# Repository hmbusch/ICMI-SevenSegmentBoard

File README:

=====================================================================
= ICMI Seven-Segment Board                                          =
=====================================================================
* Author          : Hendrik Busch
* Current version : 1.1
* License         : Creative Commons Attribution-NonCommercial-
                    ShareAlike 3.0 Germany License.

The Seven-Segment Board offers up to 8 seven-segment digits with a
control circuit made up of several cheap and easy to obtain
components.

+++++++++++++++++++++++++++++++++++++++++++++++++++++++++++++++++++++
WARNING: The current board still has a design flaw. Since the ULN2803
and the 2N7002 each incur a voltage drop when active, 5 volts is not
really enough to light the display properly when driving high refresh 
rates for the POV effect. The first counter measure given the current
design is to insert lower current limiting resistors (say 10 ohms 
instead of 150). The other measure would be to increase the voltage,
but with the current design voltage can only be increased to 7 volts
as this is the maximum voltage for the shift register and the decade
counter. So an increase from 5 to 6 volts currently seems the most 
reasonable.
The next design iteration will feature seperated supply lines for the
LED segments and the TTL logic, just to make sure.
+++++++++++++++++++++++++++++++++++++++++++++++++++++++++++++++++++++

Seven-segment LED circuit
-------------------------
The board uses dual common anode seven-segment displays, meaning that
each component feature two digits with seven segments each. Each digit
has its own anode that is common to all segments in that digit (thus
common anode) and each segment has its own cathode, resulting in two 
anodes and 14 cathodes per component. Each segment cathode of a
digit is connected to all the other cathodes for this segment on
the other digits.
The LED circuit therefore features 8 anodes (one for each digit) and
7 cathodes (one for each segment).

Switching circuit
-----------------
The switching circuit uses a minimum of I/O 5 pins (excluding power).

Two are needed for a 74HC4017 decade counter that is responsible for
sourcing power to the digits, one at a time. Using a software timer,
the decade counter switches through each digit so fast, that the
human eye cannot distinguish between the single digits being turned
on and off but sees a steady display with all eight digits lit (this
is called the POV (persistence-of-vision) effect. Exploiting this
effect, the software and circuit only have to worry about displaying
a single digit at a time and switching between digits.

In order to control what each digit is actually displaying, a shift
register (74HC595) is used to set the state of each segment. As the
shift register is not made to sink current, it is connected to an
ULN2803A darlington array. If one of the shift register pins is HIGH,
the corresponding switch in the darlington array sinks the incoming
LED current on that pin, effectively lighting the corresponding 
segment.

The software must ensure that the digit switching and the segment
configuration are in sync, otherwise the display content may show
as distorted of shifted.

Version History
---------------

- v1.1
  - The CLEAR pin of the shift register is now connected to VCC and 
    not to GND as before. Pulling it to GND in v1.0 resulted in a
	continous purge of any data loaded into the register and thus
	rendering the display unusable.

- v1.0
  - Initial revision

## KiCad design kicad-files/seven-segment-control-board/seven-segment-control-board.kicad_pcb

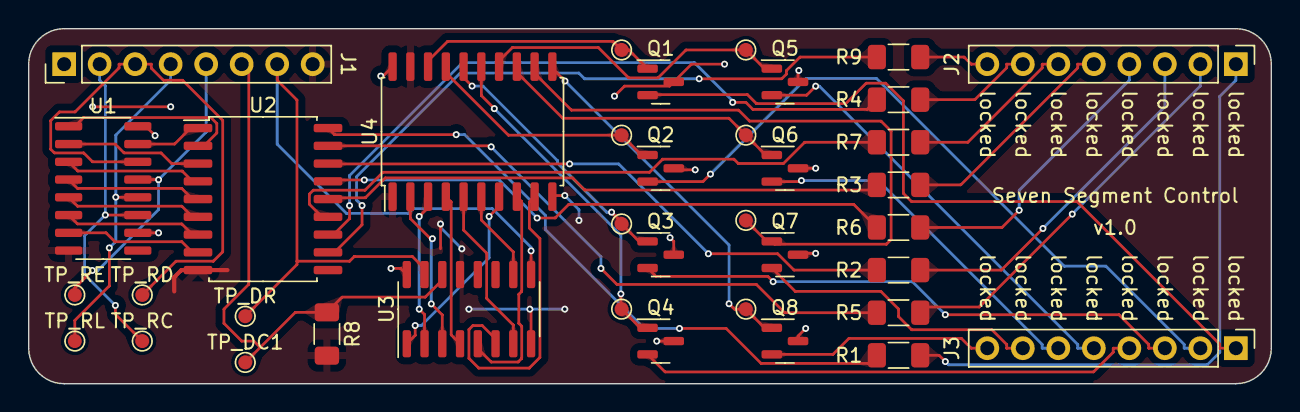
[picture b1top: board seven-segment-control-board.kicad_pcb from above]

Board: 2 copper layers, 88.9 x 25.4 mm, 38 parts (0 on the bottom side), 56 nets.

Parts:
J1: Input; PinHeader_1x08_P2.54mm_Vertical
J2: Segments; PinHeader_1x08_P2.54mm_Vertical
J3: Digits; PinHeader_1x08_P2.54mm_Vertical
Q1, Q2, Q3, Q4, Q5, Q6, Q7, Q8: BSS84; SOT-23
R1, R2, R3, R4, R5, R6, R7, R9: 150; R_1206_3216Metric_Pad1.30x1.75mm_HandSolder
R8: 10K; R_1206_3216Metric_Pad1.30x1.75mm_HandSolder
TP_DC1: TestPoint_Pad_D1.0mm
TP_DEC1, TP_DEC2, TP_DEC3, TP_DEC4, TP_DEC5, TP_DEC6, TP_DEC7, TP_DEC8: TestPoint_Pad_D1.0mm
TP_DR: TestPoint_Pad_D1.0mm
TP_RC: TestPoint_Pad_D1.0mm
TP_RD: TestPoint_Pad_D1.0mm
TP_RE: TestPoint_Pad_D1.0mm
TP_RL: TestPoint_Pad_D1.0mm
U1: 74HC595; SOIC-16_3.9x9.9mm_P1.27mm
U2: ULN2803A; SOIC-18W_7.5x11.6mm_P1.27mm
U3: 4017; SOIC-16_3.9x9.9mm_P1.27mm
U4: 74LS540; SOIC-20W_7.5x12.8mm_P1.27mm

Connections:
+5V: J1.1, Q1.3 (D), Q2.3 (D), Q3.3 (D), Q4.3 (D), Q5.3 (D), Q6.3 (D), Q7.3 (D), Q8.3 (D), U1.10 (~SRCLR), U1.16 (VCC), U3.16 (VDD), U4.20 (VCC)
/DEC_1: Q1.1 (G), TP_DEC1.1, U4.18 (Y0)
/DEC_2: Q2.1 (G), TP_DEC2.1, U4.17 (Y1)
/DEC_3: Q3.1 (G), TP_DEC3.1, U4.16 (Y2)
/DEC_4: Q4.1 (G), TP_DEC4.1, U4.15 (Y3)
/DEC_5: Q5.1 (G), TP_DEC5.1, U4.14 (Y4)
/DEC_6: Q6.1 (G), TP_DEC6.1, U4.13 (Y5)
/DEC_7: Q7.1 (G), TP_DEC7.1, U4.12 (Y6)
/DEC_8: Q8.1 (G), TP_DEC8.1, U4.11 (Y7)
/DEC_CLOCK: J1.6, R8.1, TP_DC1.1, U3.14 (CLK)
/DEC_RESET: J1.7, TP_DR.1, U3.9 (Q8), U3.15 (Reset)
/DIG_1: J3.1, Q1.2 (S)
/DIG_2: J3.2, Q2.2 (S)
/DIG_3: J3.3, Q3.2 (S)
/DIG_4: J3.4, Q4.2 (S)
/DIG_5: J3.5, Q5.2 (S)
/DIG_6: J3.6, Q6.2 (S)
/DIG_7: J3.7, Q7.2 (S)
/DIG_8: J3.8, Q8.2 (S)
/DP: J2.8, R9.1
/QA: U1.15 (QA), U2.1 (I1)
/QB: U1.1 (QB), U2.2 (I2)
/QC: U1.2 (QC), U2.3 (I3)
/QD: U1.3 (QD), U2.4 (I4)
/QE: U1.4 (QE), U2.5 (I5)
/QF: U1.5 (QF), U2.6 (I6)
/QG: U1.6 (QG), U2.7 (I7)
/QH: U1.7 (QH), U2.8 (I8)
/REG_CLOCK: J1.2, TP_RC.1, U1.11 (SRCLK)
/REG_DATA: J1.3, TP_RD.1, U1.14 (SER)
/REG_LATCH: J1.4, TP_RL.1, U1.12 (RCLK)
/SEG_A: J2.1, R1.1
/SEG_B: J2.2, R5.1
/SEG_C: J2.3, R2.1
/SEG_D: J2.4, R6.1
/SEG_E: J2.5, R3.1
/SEG_F: J2.6, R7.1
/SEG_G: J2.7, R4.1
/~REG_ENABLE: J1.5, TP_RE.1, U1.13 (~OE)
GND: J1.8, R8.2, U1.8 (GND), U2.9 (GND), U3.8 (VSS), U3.13 (CKEN), U4.1 (G1), U4.10 (GND), U4.19 (G2)
unnamed: R1.2, U2.18 (O1)
unnamed: R5.2, U2.17 (O2)
unnamed: R2.2, U2.16 (O3)
unnamed: R6.2, U2.15 (O4)
unnamed: R3.2, U2.14 (O5)
unnamed: R7.2, U2.13 (O6)
unnamed: R4.2, U2.12 (O7)
unnamed: R9.2, U2.11 (O8)
unnamed: U3.3 (Q0), U4.2 (A0)
unnamed: U3.2 (Q1), U4.3 (A1)
unnamed: U3.4 (Q2), U4.4 (A2)
unnamed: U3.7 (Q3), U4.5 (A3)
unnamed: U3.10 (Q4), U4.6 (A4)
unnamed: U3.1 (Q5), U4.7 (A5)
unnamed: U3.5 (Q6), U4.8 (A6)
unnamed: U3.6 (Q7), U4.9 (A7)

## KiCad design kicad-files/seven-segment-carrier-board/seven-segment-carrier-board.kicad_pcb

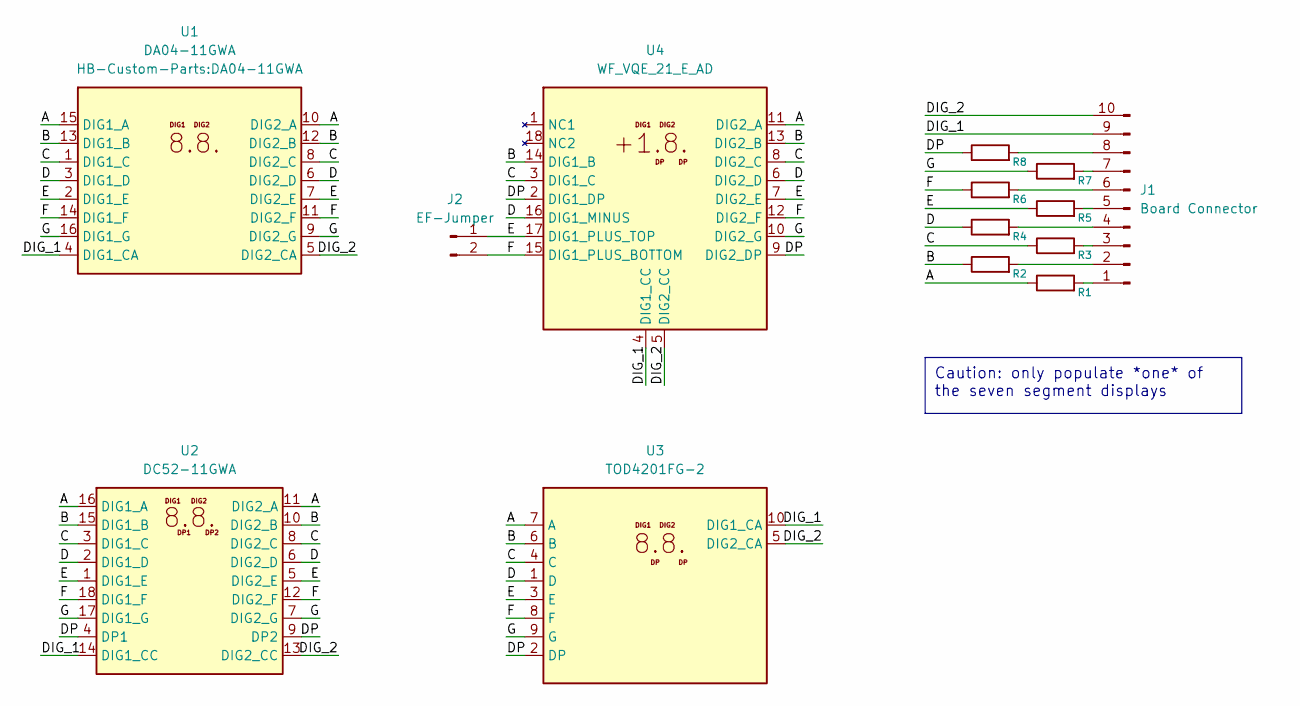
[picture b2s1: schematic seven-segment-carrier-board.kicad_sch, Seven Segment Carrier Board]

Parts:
J1: Board Connector; PinHeader_1x10_P2.54mm_Vertical
J2: EF-Jumper; SolderJumper-2_P1.3mm_Open_RoundedPad1.0x1.5mm
R1, R2, R3, R4, R5, R6, R7, R8: R; R_1206_3216Metric
U1: DA04-11GWA
U2: DC52-11GWA
U3: TOD4201FG-2
U4: WF_VQE_21_E_AD

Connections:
/A: R1.1, U1.10 (DIG2_A), U1.15 (DIG1_A), U2.11 (DIG2_A), U2.16 (DIG1_A), U3.7 (A), U4.11 (DIG2_A)
/B: R2.1, U1.12 (DIG2_B), U1.13 (DIG1_B), U2.10 (DIG2_B), U2.15 (DIG1_B), U3.6 (B), U4.13 (DIG2_B), U4.14 (DIG1_B)
/C: R3.1, U1.1 (DIG1_C), U1.8 (DIG2_C), U2.3 (DIG1_C), U2.8 (DIG2_C), U3.4 (C), U4.3 (DIG1_C), U4.8 (DIG2_C)
/D: R4.1, U1.3 (DIG1_D), U1.6 (DIG2_D), U2.2 (DIG1_D), U2.6 (DIG2_D), U3.1 (D), U4.6 (DIG2_D), U4.16 (DIG1_MINUS)
/DIG_1: J1.9, U1.4 (DIG1_CA), U2.14 (DIG1_CC), U3.10 (DIG1_CA), U4.4 (DIG1_CC)
/DIG_2: J1.10, U1.5 (DIG2_CA), U2.13 (DIG2_CC), U3.5 (DIG2_CA), U4.5 (DIG2_CC)
/DP: R8.1, U2.4 (DP1), U2.9 (DP2), U3.2 (DP), U4.2 (DIG1_DP), U4.9 (DIG2_DP)
/E: J2.1, R5.1, U1.2 (DIG1_E), U1.7 (DIG2_E), U2.1 (DIG1_E), U2.5 (DIG2_E), U3.3 (E), U4.7 (DIG2_E), U4.17 (DIG1_PLUS_TOP)
/F: J2.2, R6.1, U1.11 (DIG2_F), U1.14 (DIG1_F), U2.12 (DIG2_F), U2.18 (DIG1_F), U3.8 (F), U4.12 (DIG2_F), U4.15 (DIG1_PLUS_BOTTOM)
/G: R7.1, U1.9 (DIG2_G), U1.16 (DIG1_G), U2.7 (DIG2_G), U2.17 (DIG1_G), U3.9 (G), U4.10 (DIG2_G)
unnamed: J1.1, R1.2
unnamed: J1.2, R2.2
unnamed: J1.3, R3.2
unnamed: J1.4, R4.2
unnamed: J1.5, R5.2
unnamed: J1.6, R6.2
unnamed: J1.7, R7.2
unnamed: J1.8, R8.2

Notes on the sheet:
Caution: only populate *one* of the seven segment displays

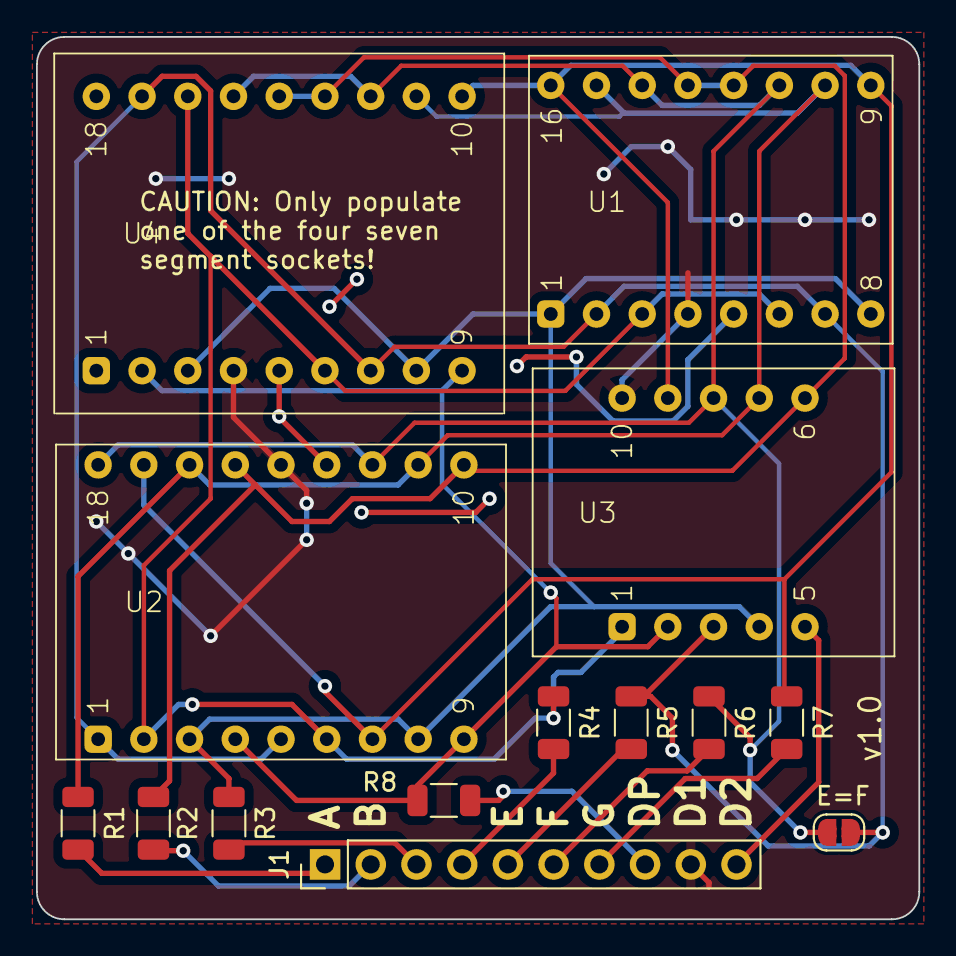
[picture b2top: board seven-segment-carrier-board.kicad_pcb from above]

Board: 2 copper layers, 49.0 x 49.0 mm, 14 parts (0 on the bottom side), 18 nets.

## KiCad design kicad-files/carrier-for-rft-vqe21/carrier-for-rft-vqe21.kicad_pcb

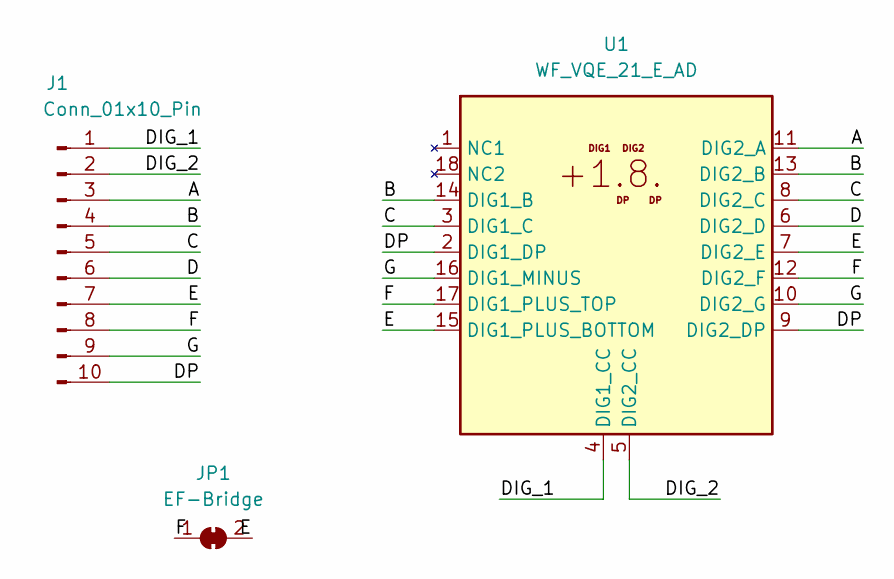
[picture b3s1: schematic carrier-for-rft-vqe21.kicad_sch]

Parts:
J1: Conn_01x10_Pin; PinHeader_1x10_P2.54mm_Vertical
JP1: EF-Bridge; SolderJumper-2_P1.3mm_Bridged_Pad1.0x1.5mm
U1: WF_VQE_21_E_AD; WF_VQE_21_E_AD_less_silk

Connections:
/A: J1.3, U1.11 (DIG2_A)
/B: J1.4, U1.13 (DIG2_B), U1.14 (DIG1_B)
/C: J1.5, U1.3 (DIG1_C), U1.8 (DIG2_C)
/D: J1.6, U1.6 (DIG2_D)
/DIG_1: J1.1, U1.4 (DIG1_CC)
/DIG_2: J1.2, U1.5 (DIG2_CC)
/DP: J1.10, U1.2 (DIG1_DP), U1.9 (DIG2_DP)
/E: J1.7, JP1.2 (B), U1.7 (DIG2_E), U1.15 (DIG1_PLUS_BOTTOM)
/F: J1.8, JP1.1 (A), U1.12 (DIG2_F), U1.17 (DIG1_PLUS_TOP)
/G: J1.9, U1.10 (DIG2_G), U1.16 (DIG1_MINUS)

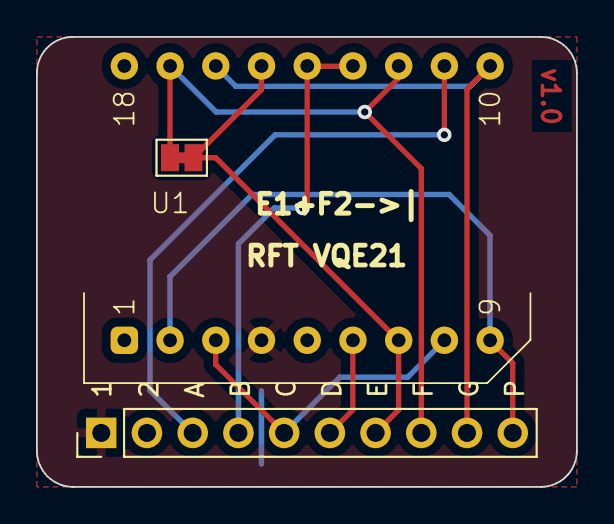
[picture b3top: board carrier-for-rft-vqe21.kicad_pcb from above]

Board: 2 copper layers, 30.0 x 25.0 mm, 3 parts (0 on the bottom side), 10 nets.

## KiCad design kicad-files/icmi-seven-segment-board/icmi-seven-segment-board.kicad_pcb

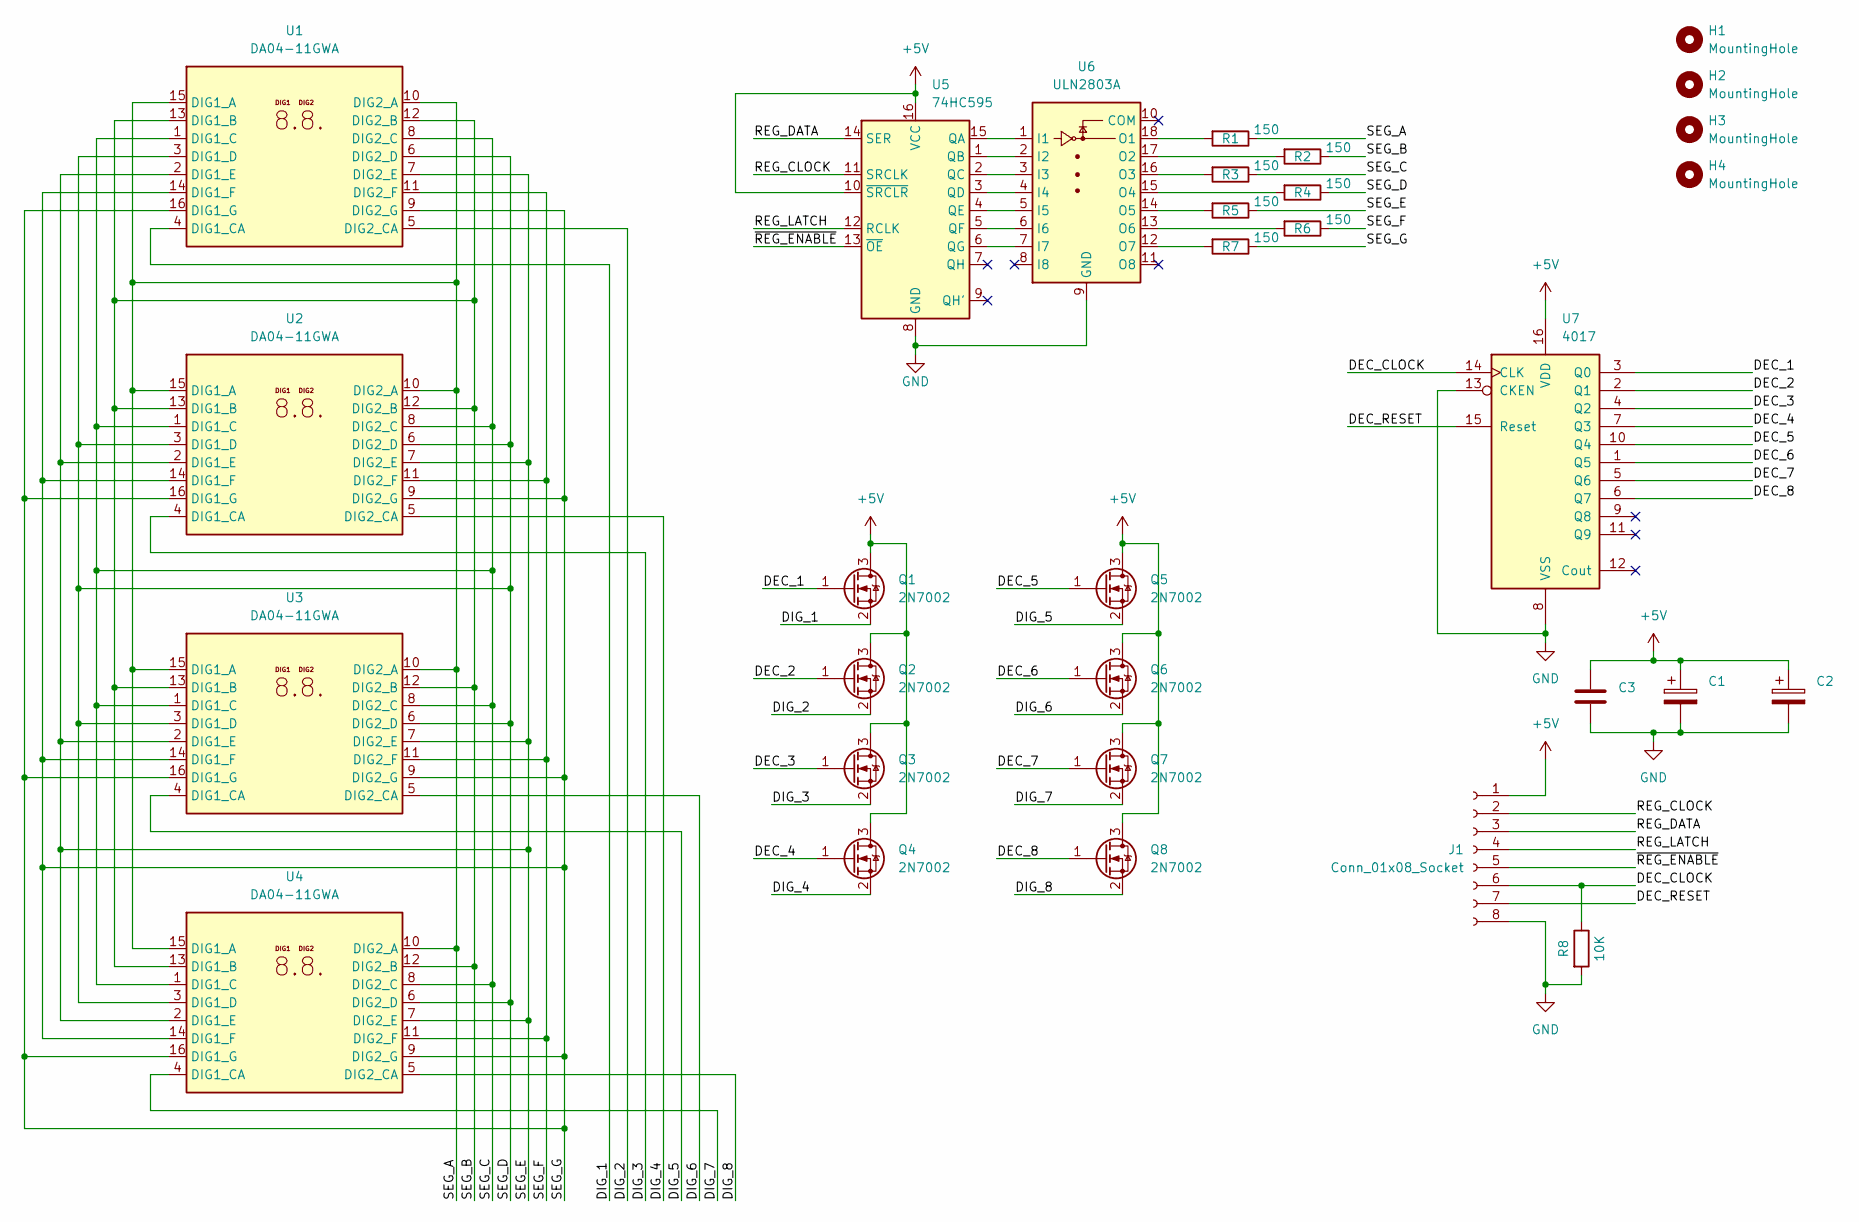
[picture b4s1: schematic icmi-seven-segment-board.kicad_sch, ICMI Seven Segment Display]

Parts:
C1: C_Polarized; CP_EIA-3216-10_Kemet-I_Pad1.58x1.35mm_HandSolder
C2: C_Polarized; CP_Elec_6.3x7.7
C3: C; C_1206_3216Metric_Pad1.33x1.80mm_HandSolder
H1, H2, H3, H4: MountingHole; MountingHole_3.2mm_M3
J1: Conn_01x08_Socket; IDC-Header_2x04_P2.54mm_Horizontal
Q1, Q2, Q3, Q4, Q5, Q6, Q7, Q8: 2N7002; SOT-23
R1, R2, R3, R4, R5, R6, R7: 150; R_1206_3216Metric_Pad1.30x1.75mm_HandSolder
R8: 10K; R_1206_3216Metric_Pad1.30x1.75mm_HandSolder
U1, U2, U3, U4: DA04-11GWA; DA04-11CGKWA
U5: 74HC595; SOIC-16_3.9x9.9mm_P1.27mm
U6: ULN2803A; SOIC-18W_7.5x11.6mm_P1.27mm
U7: 4017; SOIC-16_3.9x9.9mm_P1.27mm

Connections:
+5V: C1.1, C2.1, C3.1, J1.1, Q1.3 (D), Q2.3 (D), Q3.3 (D), Q4.3 (D), Q5.3 (D), Q6.3 (D), Q7.3 (D), Q8.3 (D), U5.10 (~SRCLR), U5.16 (VCC), U7.16 (VDD)
/DEC_1: Q1.1 (G), U7.3 (Q0)
/DEC_2: Q2.1 (G), U7.2 (Q1)
/DEC_3: Q3.1 (G), U7.4 (Q2)
/DEC_4: Q4.1 (G), U7.7 (Q3)
/DEC_5: Q5.1 (G), U7.10 (Q4)
/DEC_6: Q6.1 (G), U7.1 (Q5)
/DEC_7: Q7.1 (G), U7.5 (Q6)
/DEC_8: Q8.1 (G), U7.6 (Q7)
/DEC_CLOCK: J1.6, R8.1, U7.14 (CLK)
/DEC_RESET: J1.7, U7.15 (Reset)
/DIG_1: Q1.2 (S), U1.4 (DIG1_CA)
/DIG_2: Q2.2 (S), U1.5 (DIG2_CA)
/DIG_3: Q3.2 (S), U2.4 (DIG1_CA)
/DIG_4: Q4.2 (S), U2.5 (DIG2_CA)
/DIG_5: Q5.2 (S), U3.4 (DIG1_CA)
/DIG_6: Q6.2 (S), U3.5 (DIG2_CA)
/DIG_7: Q7.2 (S), U4.4 (DIG1_CA)
/DIG_8: Q8.2 (S), U4.5 (DIG2_CA)
/REG_CLOCK: J1.2, U5.11 (SRCLK)
/REG_DATA: J1.3, U5.14 (SER)
/REG_LATCH: J1.4, U5.12 (RCLK)
/SEG_A: R1.1, U1.10 (DIG2_A), U1.15 (DIG1_A), U2.10 (DIG2_A), U2.15 (DIG1_A), U3.10 (DIG2_A), U3.15 (DIG1_A), U4.10 (DIG2_A), U4.15 (DIG1_A)
/SEG_B: R2.1, U1.12 (DIG2_B), U1.13 (DIG1_B), U2.12 (DIG2_B), U2.13 (DIG1_B), U3.12 (DIG2_B), U3.13 (DIG1_B), U4.12 (DIG2_B), U4.13 (DIG1_B)
/SEG_C: R3.1, U1.1 (DIG1_C), U1.8 (DIG2_C), U2.1 (DIG1_C), U2.8 (DIG2_C), U3.1 (DIG1_C), U3.8 (DIG2_C), U4.1 (DIG1_C), U4.8 (DIG2_C)
/SEG_D: R4.1, U1.3 (DIG1_D), U1.6 (DIG2_D), U2.3 (DIG1_D), U2.6 (DIG2_D), U3.3 (DIG1_D), U3.6 (DIG2_D), U4.3 (DIG1_D), U4.6 (DIG2_D)
/SEG_E: R5.1, U1.2 (DIG1_E), U1.7 (DIG2_E), U2.2 (DIG1_E), U2.7 (DIG2_E), U3.2 (DIG1_E), U3.7 (DIG2_E), U4.2 (DIG1_E), U4.7 (DIG2_E)
/SEG_F: R6.1, U1.11 (DIG2_F), U2.11 (DIG2_F), U3.11 (DIG2_F), U4.11 (DIG2_F)
/SEG_G: R7.1, U1.9 (DIG2_G), U1.14 (DIG1_F), U1.16 (DIG1_G), U2.9 (DIG2_G), U2.14 (DIG1_F), U2.16 (DIG1_G), U3.9 (DIG2_G), U3.14 (DIG1_F), U3.16 (DIG1_G), U4.9 (DIG2_G), U4.14 (DIG1_F), U4.16 (DIG1_G)
/~REG_ENABLE: J1.5, U5.13 (~OE)
GND: C1.2, C2.2, C3.2, J1.8, R8.2, U5.8 (GND), U6.9 (GND), U7.8 (VSS), U7.13 (CKEN)
unnamed: U5.15 (QA), U6.1 (I1)
unnamed: U5.1 (QB), U6.2 (I2)
unnamed: U5.2 (QC), U6.3 (I3)
unnamed: U5.3 (QD), U6.4 (I4)
unnamed: U5.4 (QE), U6.5 (I5)
unnamed: U5.5 (QF), U6.6 (I6)
unnamed: U5.6 (QG), U6.7 (I7)
unnamed: R1.2, U6.18 (O1)
unnamed: R2.2, U6.17 (O2)
unnamed: R3.2, U6.16 (O3)
unnamed: R4.2, U6.15 (O4)
unnamed: R5.2, U6.14 (O5)
unnamed: R6.2, U6.13 (O6)
unnamed: R7.2, U6.12 (O7)

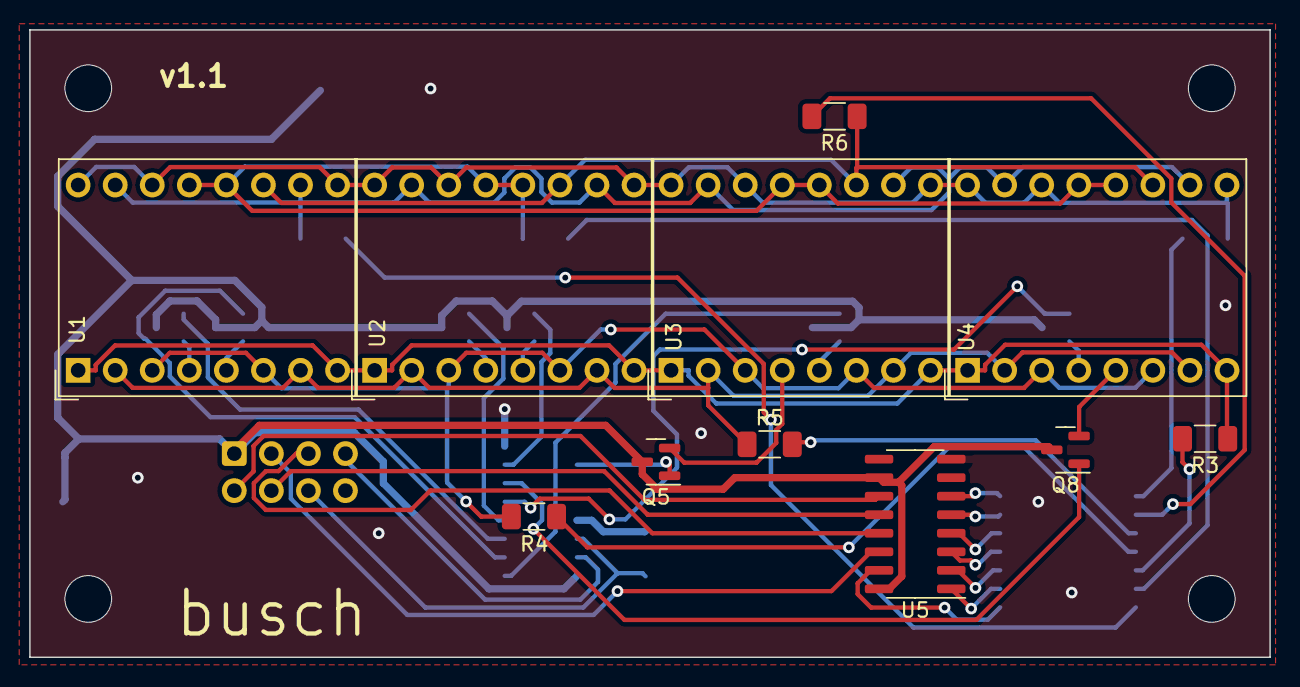
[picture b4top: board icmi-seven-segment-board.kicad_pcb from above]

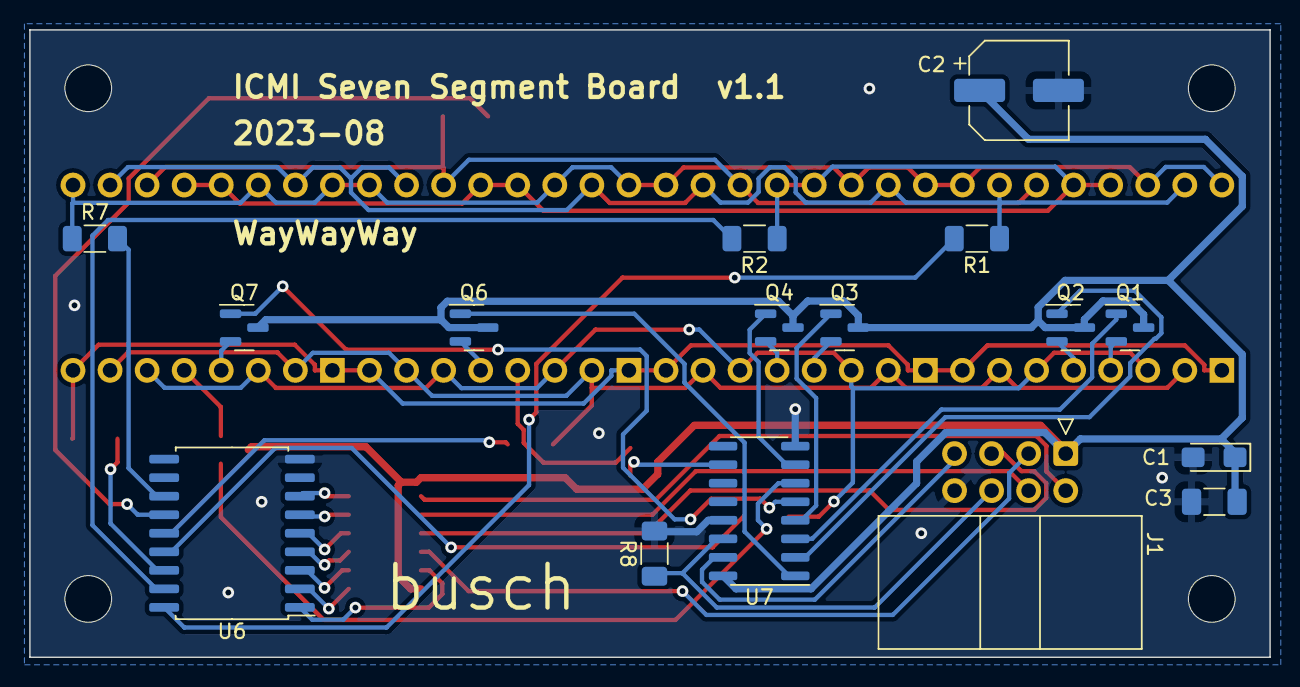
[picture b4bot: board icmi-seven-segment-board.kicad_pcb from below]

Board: 2 copper layers, 85.0 x 43.0 mm, 31 parts (16 on the bottom side), 45 nets.

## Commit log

2012-03-15 Completed the first version of a 8-digit seven segment board using a decade counter and a shift register as driver. Some components use SMD packages for smaller board size.
2012-03-20 After the first (desastrously failed) attempt to layout the seven segment PCB, the second approach looks more promising so far.
2012-03-20 Added the backups of the PCB layout to the ignored files.
2012-03-20 Hmm, this was supposed to be the commit regarding the second try on layouting the PCB. So, here it goes: the is the first step of the second try of layouting the PCB and it looks more promising so fa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
2012-03-20 Added the autorouter logfile to the list of ignored files. In this project, the autorouter doesn't seem to do much good anyway and it looks like I'm better off routing the PCB by hand.
2012-03-21 Assigned a proper name to a few more signals to make the layouting process easier (proper names enable precise filtering with the RATSNEST command)
2012-03-21 Started all over again, this time with a 2-layer PCB intended for professional manufacturing. Trying to squeeze SMD components and 'wire-intensive' parts like seven-segment displays on a single-sided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
2012-03-21 Fixed stupid bug in the circuit design: The digit anodes were all switched per seven-segment part, i.e. digit 1 was connected to the decade counter line 2 and digit 2 to decade counter line 1, and so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
2012-03-21 Finished the 2-layer PCB layout. Now all thats missing is a ground plane and some labeling.
2012-03-21 Finalized the PCB layout by adding label, ground planes and mounting holes.
2012-03-25 Duplicated some of the labels onto the bottom silkscreen layer. Especially the pin labeling is useful.
2012-04-09 Created gerber files for project
    The design was translated to gerber files using the CAM job configuration
    from Seeed Studio for their Fusion PCB service. The job generated a lot
    more files, but Fusion PCB only needs those added now.
2012-04-09 New (correct) 8-pin connector and level fix for some labels.
    Replaced the 8-pin connector with the fixed version from the library (w/
    larger pads and 1mm drill size instead of .8mm). Had to rearrange some
    wires and labels. The bottom labels were accidentally placed on bPlace
    instead of bNames, this is now also fixed.
2012-04-23 Fixed serious bug: the register's CLEAR pin is now pulled high instead of low.
    The CLEAR pin of the 74HC595 was accidentally connected to ground,
    pulling it low and thereby active all the time, preventing the register
    from working normally. It is now pulled to high and thereby inactive,
    allowing normal operation.
    The board now bears the version 1.1. The board has been updated to use the
    parts from the new sub-libraries. The last throughole resister has been
2012-05-22 Added the first version of a README
2012-05-22 Added some sample Arduino code to use with the display.
    Note: While these sketches already contain the basics for displaying
    numbers on the display, they do not contain the ability to display
    different numbers per digit yet. I will add a sketch that can do this
    soon. This sketch will then be turned into a propery library.
2012-05-25 Changed the readme after having reviewed the design problem.
2023-08-25 Redesigned the PCB in KiCad
    THe schematic and PCB was designed from scratch in KiCad and
    uses KiCad standard components.
    The design now also features some additional capacitors for
    better power stability.
    Added some production files for ordering with PCBWay (which was
    a pain in the a** and I'm not sure I will ever use them again).
2023-09-25 Seven Segment Carrier Board initial design
2023-09-26 Added a note of caution
    The board is intended for only one seven segment display at the same
    time as they may conflict in terms of polarity. A corresponding caution
    advice has been added.
2023-09-26 Added simple carrier PCB for Kingbright DA/DC04-11
    A panelized version of single module carriers should be easier to
    produce within the 100x100mm constraints of most PCB manufacturers.
2023-09-26 Added simple carrier PCB for Kingbright DA/DC52-11
    It uses the same dimensions and connector position as the one
    for DA/DC04-11.
2023-09-28 Added two additional carrier boards
    - Oasistek TOD-4201 series
    - RFT VQE 21/22 series (yes, they are *really* old)
2023-09-28 Updated the README
    I now know a little more about circuit design and had to rework
    that rather embarassing old README
2023-10-01 Designed a breadboard-friendly control board
    This control board is the first iteration towards a complete seven
    segment display board. For now, some experimentation is needed. The
    board uses basic 74HC** components and some P-channel MOSFETs to drive
    the digit anodes. The use of load switches would have inflated the
    component count as they almost always need at least 2 additional
    capacitors.
2023-10-15 Panelized control board and created JLCPCB gerber files
2023-10-15 Removed comments from design rule file
    It turns out that KiKit tries to parse this file but cannot handle lines
    starting with a hash (#) symbol, throwing an error.
2023-10-15 Created panelized production files for Kingbright Carrier
    These board have been panelized using KiKit, the settings have been
    added.
2023-10-15 Changed control board panelization to KiKit
    No use in hand-paneling a simple 1x3 layout when KiKit can do the same
    automatically. The panelized PCB file has been updated and the
    production ZIP has been regenerated with the new layout.
    The design rules had to be modified, KiKit cannot handle comments in the
    DRU file, resulting in _Expected '(' got '#'_ errors.
2023-11-10 Added a SVG drawing and a photo of the control board
    The drawing was made using PCBDraw, configured with the `remap.json`
    and the `styles.json`. There are currently no package SVGs available
    for the ICs and the SOT-23 components had to be rotated after
    generating the SVG.
    The photo show the fully populated board minus the header pins.
